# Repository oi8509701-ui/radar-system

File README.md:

X-Band T/R Module (10 GHz) with Fractal Antenna

High-performance single-channel Transmit/Receive (T/R) module for X-band phased array systems (~10–10.5 GHz), featuring integrated beamforming and a compact fractal antenna.
---------------------------------

---------------------------------

High-performance single-channel Transmit/Receive (T/R) module for X-band phased array systems (~10–10.5 GHz), featuring integrated beamforming and a compact fractal antenna.

⸻
 
 Overview

This project implements a single RF front-end module (tile) designed for scalable phased array systems.

Key features:

	•	X-band operation (~10–10.5 GHz)
	•	Integrated PA + LNA + T/R switch (QPM1002)
	•	Beamforming support (phase + amplitude control)
	•	Compact fractal antenna (14×14 mm)
	•	Designed for array scaling (e.g., 256+ elements)
	•	Optimized for automated routing (Freerouting)

⸻
 
 Architecture

RF IN → Phase Shifter → Attenuator → TXIN → [QPM1002] → ANT → Antenna
                                            ▲
RF OUT ← Phase Shifter ← Attenuator ← RXOUT ┘

QPM1002 Internal Structure:

	•	TX path: PA (~35 dBm pulsed)
	•	RX path: LNA (~2.2 dB NF, ~25 dB gain)
	•	Internal T/R switch
	•	Built-in power detector (VDET)

⸻
 
 Power Architecture

Rail	Voltage	Purpose
TX_VD	+25V	Power Amplifier
RX_VD	+10V	LNA
VDD_LOGIC	+5V	Digital logic
VDD_IO	+3.3V	Control interface
VG	-2.5V	GaN gate bias

Converters:

	•	LM5156 (SEPIC) → 25V
	•	LM5017 → 10V / 5V
	•	Charge pump → -2.5V

⸻

RF Components

Component	Function	Notes

QPM1002	T/R front-end	Core RF IC
TGP2109	Phase shifter (6-bit)	8–12 GHz
PE43705	Attenuator (6-bit)	0.5–12 GHz

⸻

 PCB
 
	•	Substrate: Rogers 4350B
	•	Stackup: 4 layers (RF + GND + PWR + CTRL)
	•	Controlled impedance (50 Ω)
	•	Dense via stitching for RF grounding
	•	Optimized for high-frequency layout

⸻

 Thermal Design

Per module dissipation:

Block	Power
PA	~8 W
DC-DC	~5.5 W
Beamforming	~1.3 W
Other	~1 W

Total: ~16 W per module

For 256 modules:

	•	Total ≈ 4 kW
	•	Requires liquid cooling

⸻
 
 Control Interface
 
	•	SPI (phase + attenuation control)
	•	GPIO (TX/RX switching)
	•	I²C (temperature sensors)

Logic:

	•	SN74HC595 (shift register)
	•	SN74LVTH573 (latch)

⸻
 
 Monitoring
 
	•	4× TMP117 temperature sensors:
	•	RF front-end
	•	Power stage
	•	Beamforming chain
	•	PCB ambient

⸻
 
 Power Sequencing

Power-Up:

	1.	Apply VG (-2.5V)
	2.	Disable TX/RX
	3.	Enable RX_VD (10V)
	4.	Enable TX_VD (25V)
	5.	Enable TX/RX

Power-Down:

	1.	Disable TX/RX
	2.	Disable TX_VD
	3.	Disable RX

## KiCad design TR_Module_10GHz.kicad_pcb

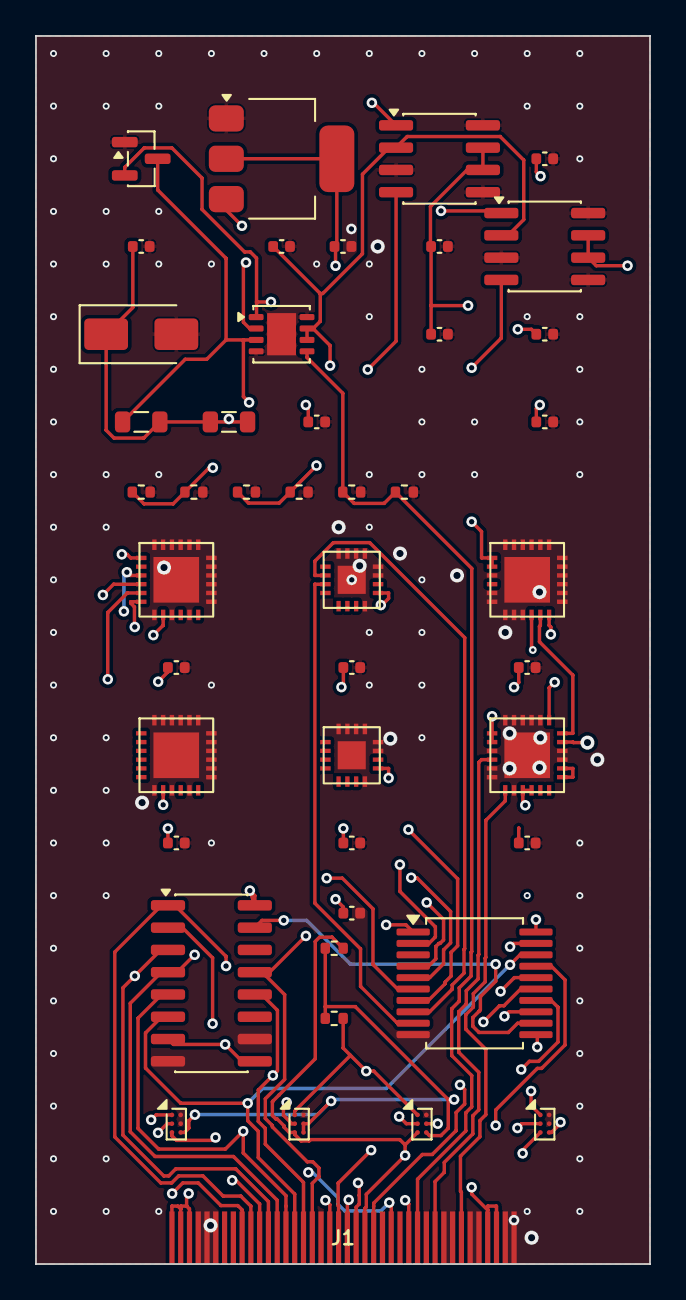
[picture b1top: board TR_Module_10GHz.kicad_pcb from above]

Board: 4 copper layers, 35.0 x 70.0 mm, 45 parts (0 on the bottom side), 39 nets.

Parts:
C10, C11, C12, C13, C14, C15, C16, C17, C18, C19, C20, C21, C22, C23, C24, C25: 100nF; C_0402_1005Metric
D1: TVS; D_SMA
J1: Card Edge 40-pin
L1: EMI; L_0805_2012Metric
L2: 22uH; L_0805_2012Metric
Q1: MOSFET; SOT-23
R1: FB10V_h; R_0402_1005Metric
R2: FB10V_l; R_0402_1005Metric
R3: FB5V_h; R_0402_1005Metric
R4: FB5V_l; R_0402_1005Metric
R5: FBSEP_h; R_0402_1005Metric
R6: FBSEP_l; R_0402_1005Metric
R7: SDA_PU; R_0402_1005Metric
R8: SCL_PU; R_0402_1005Metric
U1: LM5156 SEPIC; VSON-8-1EP_3x3mm_P0.65mm_EP1.65x2.4mm
U2: LM5017 10V; SOIC-8_3.9x4.9mm_P1.27mm
U3: LM5017 5V; SOIC-8_3.9x4.9mm_P1.27mm
U4: ACT43750; QFN-24_4x4mm_P0.5mm
U5: LDO 3.3V; SOT-223-3_TabPin2
U6: QPM1002; QFN-24_4x4mm_P0.5mm
U7: TGP2109 TX; QFN-24_4x4mm_P0.5mm
U8: TGP2109 RX; QFN-24_4x4mm_P0.5mm
U9: QPC0045 TX; QFN-16_3x3mm_P0.5mm
U10: QPC0045 RX; QFN-16_3x3mm_P0.5mm
U11: SN74HC595; SOIC-16_3.9x9.9mm_P1.27mm
U12: SN74LVTH573; SSOP-20_5.3x7.2mm_P0.65mm
U13: TMP117 QPM1002; Texas_DSBGA-6_0.9x1.4mm_Layout2x3_P0.5mm
U14: TMP117 SEPIC; Texas_DSBGA-6_0.9x1.4mm_Layout2x3_P0.5mm
U15: TMP117 PS; Texas_DSBGA-6_0.9x1.4mm_Layout2x3_P0.5mm
U16: TMP117 PCB; Texas_DSBGA-6_0.9x1.4mm_Layout2x3_P0.5mm

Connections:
+3V3: C24.1, C25.1, R7.1, R8.1, U5.2, U13.C2, U14.B2, U14.C2, U15.C2, U16.C2
+5V: C10.1, C13.1, C14.1, C15.1, C16.1, C17.1, C18.1, C19.1, C20.1, C23.1, U3.6, U3.7, U4.1, U4.2, U5.3, U6.1, U6.2, U7.8, U8.8, U9.9, U10.9, U11.16, U12.20, U15.B2
+10V: C12.1, C22.1, U2.6, U2.7, U6.9, U6.10
+25V: U6.13, U6.14
+VIN: C11.1, C21.1, D1.1, J1.1, J1.2, J1.3, J1.37, J1.38, L1.1, L1.2, L2.2, U1.6, U1.7, U2.2, U3.2
BOOT_5V: J1.20, U3.1
BOOT_10V: J1.19, U1.2, U2.1
CTRL_TX_ATT0: U9.2, U12.8
CTRL_TX_ATT1: U9.3, U12.9
CTRL_TX_PS0: U7.1, U12.2
CTRL_TX_PS1: U7.2, U12.3
CTRL_TX_PS2: U7.3, U12.4
CTRL_TX_PS3: U7.4, U12.5
CTRL_TX_PS4: U7.5, U12.6
CTRL_TX_PS5: U7.6, U12.7
EN_BOOST: J1.22, Q1.2, U1.1
FB_5V: J1.28, R3.1, R4.1, U3.4
FB_10V: J1.27, R1.1, R2.1, U2.4
FB_SEPIC: J1.29, R5.1, R6.1, U1.5
GND: C10.2, C11.2, C12.2, C13.2, C14.2, C15.2, C16.2, C17.2, C18.2, C19.2, C20.2, C21.2, C22.2, C23.2, C24.2, C25.2, D1.2, J1.4, J1.5, J1.6, J1.18, J1.30, J1.32, J1.33, J1.35, J1.36, J1.39, J1.40, Q1.1, R1.2, R2.2, R3.2, R4.2, R5.2, R6.2, U1.4, U1.8, U1.9, U2.3, U2.5, U2.8, U3.3, U3.5, U3.8, U4.3, U4.5, U4.6, U4.7, U4.8, U4.9, U4.13, U4.14, U4.15, U4.16, U4.17, U4.18, U4.19, U4.20, U4.21, U4.22, U4.23, U4.24, U4.25, U5.1, U6.3, U6.5, U6.6, U6.8, U6.15, U6.16, U6.20, U6.21, U6.22, U6.23, U6.24, U6.25, U7.7, U7.9, U7.11, U7.13, U7.14, U7.15, U7.16, U7.17, U7.18, U7.19, U7.20, U7.21, U7.22, U7.23, U7.24, U7.25, U8.7, U8.9, U8.11, U8.13, U8.14, U8.15, U8.16, U8.17, U8.18, U8.19, U8.20, U8.21, U8.22, U8.23, U8.24, U8.25, U9.8, U9.11, U9.12, U9.13, U9.14, U9.15, U9.16, U9.17, U10.8, U10.11, U10.12, U10.13, U10.14, U10.15, U10.16, U10.17, U11.8, U11.10, U12.10, U13.A2, U13.B2, U14.A2, U15.A2, U16.A2, U16.B2
I2C_SCL: J1.24, R8.2, U13.A1, U14.A1, U15.A1, U16.A1
I2C_SDA: J1.23, R7.2, U13.C1, U14.C1, U15.C1, U16.C1
RXSW: U4.11, U6.18
RX_RF_OUT: J1.34, U6.7
SR_OE_N: J1.17, U11.13, U12.1
SR_QA: J1.9, U11.15, U12.12
SR_QB: J1.10, U11.1, U12.13
SR_QC: J1.11, U11.2, U12.14
SR_QD: J1.12, U11.3, U12.15
SR_QE: J1.13, U11.4, U12.16
SR_QF: J1.14, U11.5, U12.17
SR_QG: J1.15, U11.6, U12.18
SR_QH: U11.7, U11.9, U12.19
SR_RCLK: J1.16, U11.12, U12.11
SW_SEPIC: J1.26, L2.1, Q1.3, U1.3
TMP_ALERT: J1.25, U13.B1, U14.B1, U15.B1, U16.B1
TXSW: U4.10, U6.17
TX_RF_IN: J1.31, U6.4
VG: J1.21, U4.12, U6.19

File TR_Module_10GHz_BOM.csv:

value,footprint,quantity,references
100nF,Capacitor_SMD:C_0402_1005Metric,11,"['C20', 'C19', 'C18', 'C17', 'C16', 'C15', 'C14', 'C13', 'C12', 'C11', 'C10']"
SN74LVTH573,Package_SO:SSOP-20_5.3x7.2mm_P0.65mm,1,['U12']
SN74HC595,Package_SO:SOIC-16_3.9x9.9mm_P1.27mm,1,['U11']
MountingHole_2.7mm,,4,"['MH2', 'MH3', 'MH1', 'MH4']"
TMP117 SEPIC,Package_BGA:Texas_DSBGA-6_0.9x1.4mm_Layout2x3_P0.5mm,1,['U14']
TMP117 PS,Package_BGA:Texas_DSBGA-6_0.9x1.4mm_Layout2x3_P0.5mm,1,['U15']
QPC0045 TX,TR_Module_Lib:QFN-16_3x3mm_P0.5mm,1,['U9']
LM5017 10V,Package_SO:SOIC-8_3.9x4.9mm_P1.27mm,1,['U2']
LM5156 SEPIC,Package_SON:VSON-8-1EP_3x3mm_P0.65mm_EP1.65x2.4mm,1,['U1']
QPM1002,TR_Module_Lib:QFN-24_4x4mm_P0.5mm,1,['U6']
LM5017 5V,Package_SO:SOIC-8_3.9x4.9mm_P1.27mm,1,['U3']
TGP2109 TX,TR_Module_Lib:QFN-24_4x4mm_P0.5mm,1,['U7']
TGP2109 RX,TR_Module_Lib:QFN-24_4x4mm_P0.5mm,1,['U8']
ACT43750,TR_Module_Lib:QFN-24_4x4mm_P0.5mm,1,['U4']
TMP117 QPM1002,Package_BGA:Texas_DSBGA-6_0.9x1.4mm_Layout2x3_P0.5mm,1,['U13']
QPC0045 RX,TR_Module_Lib:QFN-16_3x3mm_P0.5mm,1,['U10']
TMP117 PCB,Package_BGA:Texas_DSBGA-6_0.9x1.4mm_Layout2x3_P0.5mm,1,['U16']

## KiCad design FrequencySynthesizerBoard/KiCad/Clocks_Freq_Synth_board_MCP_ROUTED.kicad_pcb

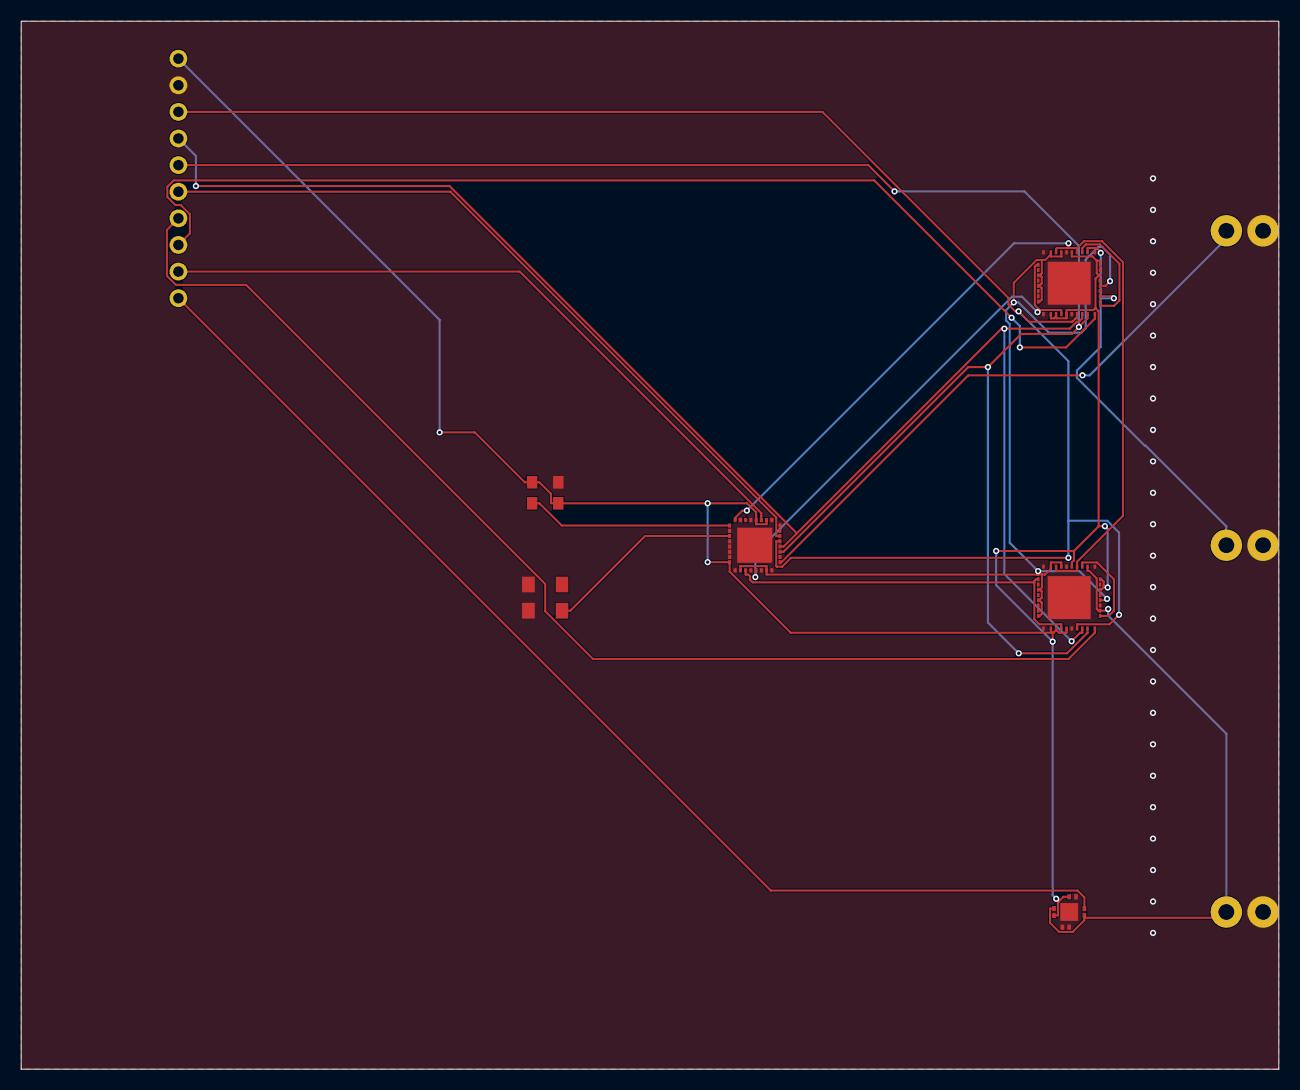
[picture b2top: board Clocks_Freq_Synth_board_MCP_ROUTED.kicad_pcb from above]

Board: 2 copper layers, 120.0 x 100.0 mm, 10 parts (0 on the bottom side), 21 nets.

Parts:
J1: SMA_TX_LO; SMA_Amphenol_132133-01-2X_Horizontal
J2: SMA_RX_LO; SMA_Amphenol_132133-01-2X_Horizontal
J3: SMA_REF_OUT; SMA_Amphenol_132133-01-2X_Horizontal
J4: CTRL_INTERFACE; PinSocket_1x10_P1.27mm_Vertical
U1: AD9523-1; LFCS-32-1EP_5x5mm_P0.5mm_EP3.35x3.35mm
U2, U3: ADF4382ABCCZ; LFCC-40-1EP_6x6mm_P0.5mm_EP4.1x4.1mm
U4: HMC1118; LFCS-8-1EP_3x3mm_P0.65mm_EP1.7x1.7mm
Y1: 100MHz OCXO; Oscillator_SMD_EuropeanQuartz_3225-4Pin
Y2: 25MHz TCXO; Oscillator_SMD_EuropeanQuartz_2520-4Pin

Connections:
CLK_25M: U1.1, Y2.4
CLK_100M: U1.3, Y1.3
CLK_DIST_RX: U1.13, U3.1, U3.12
CLK_DIST_TX: U1.11, U2.1, U2.12
CS_U1: J4.6, U1.22
CS_U2: J4.7, U2.18
CS_U3: J4.8, U3.18
GND: J1.2, J2.2, J3.2, J4.2, U1.2, U1.4, U1.5, U1.6, U1.7, U1.9, U1.12, U1.14, U1.16, U1.18, U1.24, U1.25, U1.29, U1.31, U1.EP, U2.2, U2.4, U2.6, U2.7, U2.9, U2.14, U2.21, U2.23, U2.25, U2.27, U2.32, U2.36, U2.EP, U3.2, U3.4, U3.6, U3.7, U3.9, U3.14, U3.21, U3.23, U3.25, U3.27, U3.32, U3.36, U3.EP, U4.3, U4.4, U4.7, U4.EP, Y1.1, Y1.4, Y2.2
RF_REF: J3.1, U1.17
RF_RX_N: U3.19, U3.29
RF_RX_P: J2.1, U3.20, U3.28
RF_SW_CTRL: J4.10, U4.6
RF_TX_N: U2.19, U2.29
RF_TX_P: J1.1, U2.20, U2.28, U4.1, U4.5
SPI_CLK: J4.3, U1.21, U2.15, U3.15
SPI_MISO: J4.5, U1.19, U2.17, U3.17
SPI_MOSI: J4.4, U1.20, U2.16, U3.16
U1_SYNC: J4.9, U1.27
VCP: U1.32, U2.30, U2.34, U3.30, U3.34
VDD_1V8: U1.10, U1.15, U1.30, U2.3, U2.5, U2.8, U2.22, U2.33, U2.35, U3.3, U3.5, U3.8, U3.22, U3.33, U3.35
VDD_3V3: J4.1, U1.8, U1.26, U1.28, U2.10, U2.11, U2.13, U2.24, U2.26, U2.31, U3.10, U3.11, U3.13, U3.24, U3.26, U3.31, U4.2, U4.8, Y2.1, Y2.3

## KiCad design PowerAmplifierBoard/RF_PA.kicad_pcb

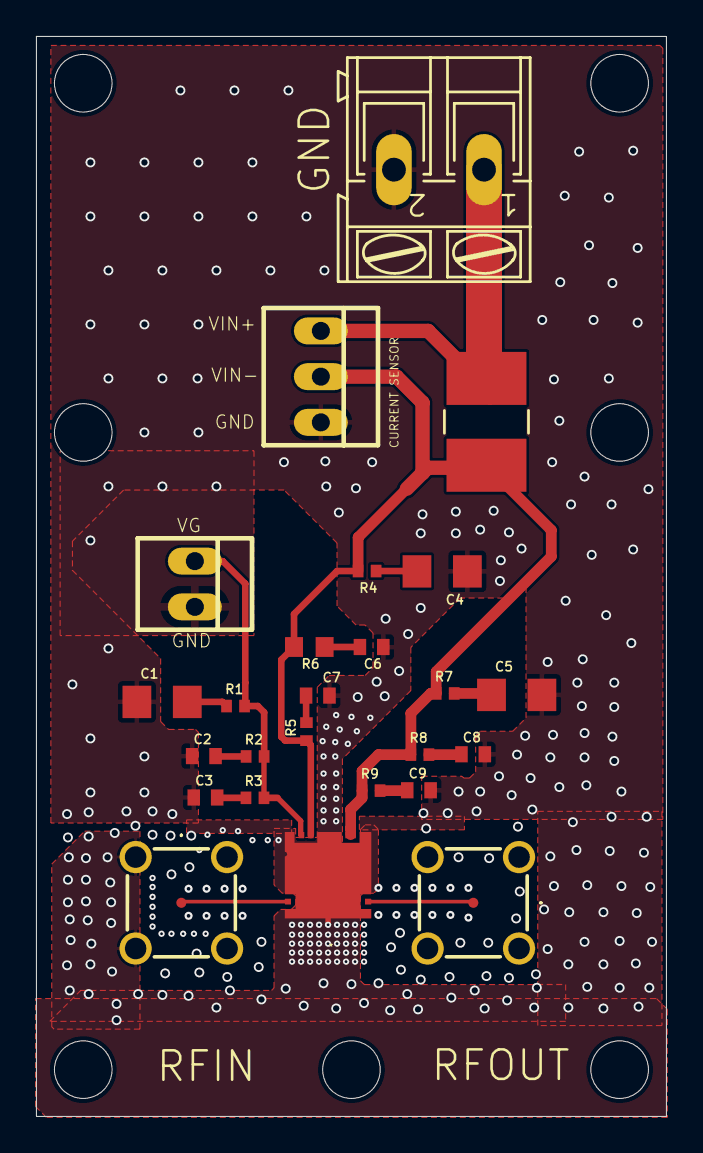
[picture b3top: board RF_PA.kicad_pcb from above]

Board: 4 copper layers, 35.0 x 60.0 mm, 32 parts (0 on the bottom side), 15 nets.

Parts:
C1, C4, C5: 10µF; C1206_334
C2, C3, C6, C7, C8, C9: 0.1µF; C0402_334
J1, J2: 142-0731-211; 1420731211
R1, R4: 10R; R0402_334
R2, R3, R5, R7, R8, R9: 0R; R0402_334
R6: 0R; R0603_334
R10: 5mR; WSL2816_VIS
U$1: QPA2962_B
UNK22V0: AK300_2_181
UNK_HOLE_0: dummyfp0
UNK_HOLE_1: dummyfp1
UNK_HOLE_2: dummyfp2
UNK_HOLE_3: dummyfp3
UNK_HOLE_4: dummyfp4
UNK_HOLE_5: dummyfp5
UNK_HOLE_6: dummyfp6
X2: 22-23-2021; 22-23-2021_165
X3: 22-23-2031; 22-23-2031_165

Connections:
GND: C1.1, C2.1, C3.1, C4.1, C5.2, C6.1, C7.1, C8.2, C9.2, J1.2, J1.3, J1.4, J1.5, J2.2, J2.3, J2.4, J2.5, U$1.GND, UNK22V0.2, X2.2, X3.3
unnamed: C3.2, R3.1
unnamed: J1.1, U$1.RFIN
unnamed: C1.2, R1.1
unnamed: C2.2, R2.1
unnamed: C4.2, R4.1
unnamed: C6.2, R6.1
unnamed: C7.2, R5.1
unnamed: J2.1, U$1.RFOUT
unnamed: C5.1, R7.2
unnamed: C8.1, R8.2
unnamed: C9.1, R9.2
VD: R10.2, UNK22V0.1, X3.1
VG: R1.2, R2.2, R3.2, U$1.VG, X2.1
VIN_M: R4.2, R5.2, R6.2, R7.1, R8.1, R9.1, R10.1, U$1.VD1, U$1.VD2, X3.2

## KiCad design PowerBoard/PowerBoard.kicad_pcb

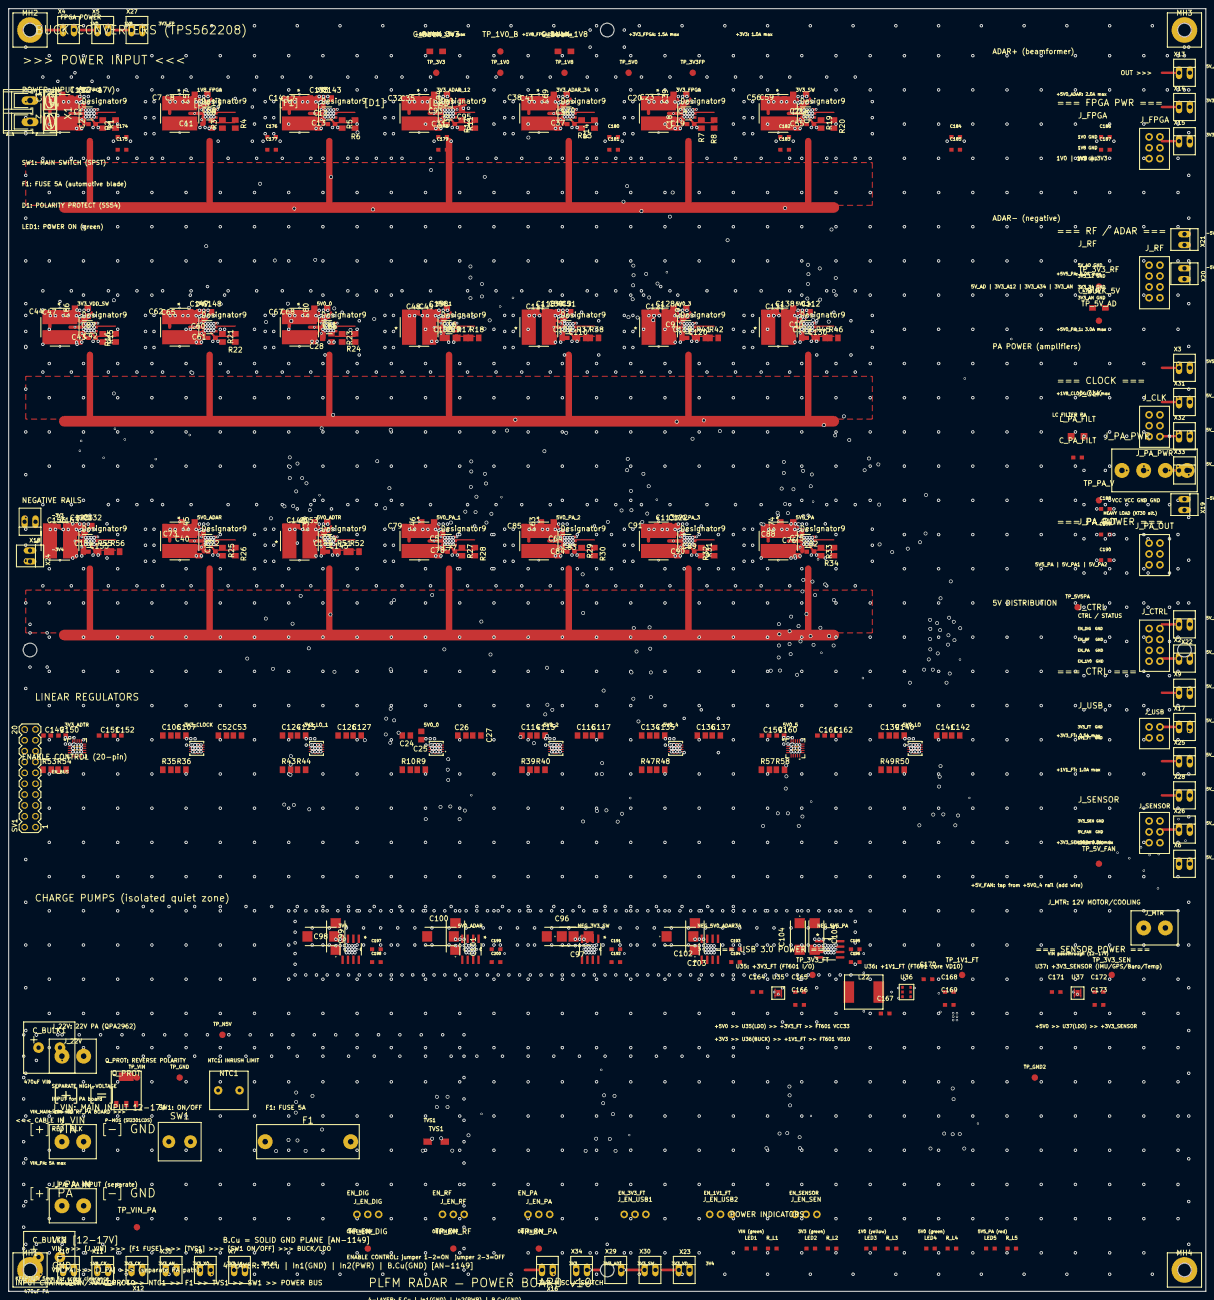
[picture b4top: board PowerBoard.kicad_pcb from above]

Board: 2 copper layers, 280.0 x 300.0 mm, 427 parts (0 on the bottom side), 163 nets.

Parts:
C1, C6, C12, C18, C29, C30, C36, C42, C54, C60, C66, C71, C76, C77, C83, C89, C109, C119, C129, C144, C154: 0.1µF; C0805
C2, C3, C7, C8, C11, C13, C14, C17, C19, C20, C23, C31, C32, C35, C37, C38, C41, C43, C44, C47, C48, C49, C55, C56, C59, C61, C62, C65, C67, C68, C72, C73, C78, C79, C82, C84, C85, C88, C90, C91, C110, C111, C120, C121, C130, C131, C145, C146, C149, C155, C156, C159: 22µF; C0603
C4, C5, C9, C10, C15, C16, C21, C22, C24, C25, C28, C33, C34, C39, C40, C45, C46, C50, C51, C52, C53, C57, C58, C63, C64, C69, C70, C74, C75, C80, C81, C86, C87, C92, C93, C94, C95, C108, C112, C113, C114, C115, C118, C122, C123, C124, C125, C128, C132, C133, C134, C135, C138, C139, C140, C143, C147, C148, C157, C158: 10µF; C0805
C26, C27, C106, C107, C116, C117, C126, C127, C136, C137, C141, C142: 1µF; C0805
C96, C97, C98, C99, C100, C101, C102, C103, C104, C105: T521W476M020ATE045; T521W
C150, C152, C160, C162: 10nF; C0603
C151, C153, C161, C163: 10µF; C0603
C164, C165, C167, C171, C172: 10uF; C0805
C166, C173: 1uF; C0805
C168, C169: 22uF; C0805
C170: 100nF; C0805
C174, C176, C178, C180, C182, C184, C186: 10uF VIN; C0805_BUS
C175, C177, C179, C181, C183, C185, C187: 100nF VIN; C0805_BUS
C188: 47uF PA; C0805_BUS
C189: 10uF PA; C0805_BUS
C190: 100nF PA; C0805_BUS
C191: 10uF -3V3_SW; C0805_FILT
C192: 100nF -3V3_SW; C0805_FILT
C193: 10uF -5V0_ADAR34; C0805_FILT
C194: 100nF -5V0_ADAR34; C0805_FILT
C195: 10uF -5V5_PA; C0805_FILT
C196: 100nF -5V5_PA; C0805_FILT
C197: 10uF -3V4; C0805_FILT
C198: 100nF -3V4; C0805_FILT
C199: 10uF -5V0_ADAR12; C0805_FILT
C200: 100nF -5V0_ADAR12; C0805_FILT
C_BULK1, C_BULK2: 470uF/25V; Capacitor_THT_D10_P5mm
C_BULK_1V8: 22uF/6.3V; Cap_1210_22uF
C_BULK_3V3: 47uF/6.3V; Cap_1210_47uF
C_BULK_5V: 47uF/10V; Cap_1210_47uF
C_PA_FILT: 10uF/10V; Cap_0805_PA
F1: FUSE 5A; Fuse_Holder_5x20
J_22V: 22V PA INPUT; AK300_2_NEW
J_CLK: CLOCK_PWR; PinHeader_2xN_P2.54mm
J_CTRL: CTRL/STATUS; PinHeader_2x4_P2.54mm
J_EN_DIG: EN_DIGITAL; Jumper_1x03_P2.54mm
J_EN_PA: EN_PA; Jumper_1x03_P2.54mm
J_EN_RF: EN_RF; Jumper_1x03_P2.54mm
J_EN_SEN: EN_SENSOR; Jumper_1x03_P2.54mm
J_EN_USB1: EN_3V3_FT; Jumper_1x03_P2.54mm
J_EN_USB2: EN_1V1_FT; Jumper_1x03_P2.54mm
J_FPGA: FPGA_PWR; PinHeader_2xN_P2.54mm
J_MTR: MOTOR/FAN 12V; AK300_2_NEW
J_PA_IN: VIN_PA; AK300_2_NEW
J_PA_OUT: PA_PWR; PinHeader_2xN_P2.54mm
J_PA_PWR: PA_POWER_OUT; ScrewTerminal_4pin_5.08mm
J_RF: RF_ADAR_PWR; PinHeader_2xN_P2.54mm
J_SENSOR: SENSOR_PWR; PinHeader_2xN_P2.54mm
J_USB: USB_PWR; PinHeader_2xN_P2.54mm
J_VIN: VIN_MAIN 12-17V; AK300_2_NEW
L1, L9: 2.2µH; IND_VLP8040T-1R0N_TDK
L2, L3, L4, L5, L6, L7, L8, L10, L11, L12, L13, L14, L15, L16, L17, L18, L19, L20, L21: 3.3µH; IND_VLP8040T-1R0N_TDK
L22: 1uH; IND_VLP8040T
LED1, LED2, LED3, LED4, LED5: LED; LED_0805
L_PA_FILT: 4.7uH/3A; Inductor_1210
MH1, MH2, MH3, MH4: M3; MountingHole_M3
NTC1: 5D-9 NTC; NTC_Radial_5mm
Q_PROT: Si2301CDS; SOT-223_P-MOS
R1: 3.09k; M0805
R2, R4, R6, R8, R10, R12, R14, R16, R18, R20, R22, R24, R26, R28, R30, R32, R34, R36, R38, R40, R42, R44, R46, R48, R50, R52, R56: 10k; M0805
R3: 13.7k; M0805
R5, R7, R11, R13, R15, R19: 32.2k; M0805
R9, R35, R43, R47: 12k; M0805
R17, R23, R25, R27, R29, R31, R37, R41, R45, R51, R55: 56.2k; M0805
R21: 34.8k; M0805
R33: 61.9k; M0805
R39: 2k; M0805
R49: 23.4k; M0805
R53, R57: 35.7k; M0805
R54, R58: 11.5k; M0805
R_L1, R_L2, R_L3, R_L4, R_L5: 1k; R_0805_LED
SV1: MA10-2
SW1: MAIN POWER; SW_SPST_Toggle
TP_1V0, TP_1V0_B: +1V0_FPGA; TestPoint_1.5mm
TP_1V1_FT: +1V1_FT; TestPoint_1.5mm
TP_1V8: +1V8_FPGA; TestPoint_1.5mm
TP_3V3: +3V3; TestPoint_1.5mm
TP_3V3FP: +3V3_FPGA; TestPoint_1.5mm
TP_3V3_FT: +3V3_FT; TestPoint_1.5mm
TP_3V3_RF: +3V3_ADAR_12; TestPoint_1.5mm
TP_3V3_SEN: +3V3_SENSOR; TestPoint_1.5mm
TP_5V0: +5V0_4; TestPoint_1.5mm
TP_5V5PA: +5V5_PA; TestPoint_1.5mm
TP_5V_AD: +5V0_ADAR; TestPoint_1.5mm
TP_5V_FAN: +5V_FAN; TestPoint_1.5mm
TP_EN_DIG: EN_+3V3_FPGA; TestPoint_1.5mm
TP_EN_PA: EN_+5V5_PA; TestPoint_1.5mm
TP_EN_RF: EN_+5V0_ADAR; TestPoint_1.5mm
TP_GND, TP_GND2: GND; TestPoint_1.5mm
TP_N5V: -5V0_ADAR12; TestPoint_1.5mm
TP_PA_V: +5V5_PA; TestPoint_1.5mm
TP_VIN: VIN; TestPoint_1.5mm
TP_VIN_PA: VIN; TestPoint_1.5mm
TVS1: SMAJ18A; TVS_SMA
U1, U2, U3, U4, U6, U7, U8, U9, U10, U11, U12, U13, U14, U15, U16, U17, U24, U26, U28, U31, U33: TPS562208DDCT; DDC0006A_N
U5, U23, U25, U27, U29, U30: ADM7151ACPZ-04-R7; CP_8_11_ADI
U18, U19, U20, U21, U22: LM2662MX/NOPB; M08A
U32, U34: TPS7A8300RGRR; RGR20_2P05X2P05_TEX
U35: ADM7151 3V3_FT; CP_8_11_ADI
U36: TPS562208 1V1_FT; DDC0006A_N
U37: ADM7151 3V3_SEN; CP_8_11_ADI
UNK_HOLE_0: dummyfp0
UNK_HOLE_1: dummyfp1
UNK_HOLE_2: dummyfp2
UNK_HOLE_3: dummyfp3
UNK_HOLE_4: dummyfp4
UNK_HOLE_5: dummyfp5
UNK_HOLE_6: dummyfp6
UNK_HOLE_7: dummyfp7
X1: AK300_2
X2, X3, X4, X5, X6, X7, X8, X9, X10, X11, X12, X13, X14, X15, X16, X17, X18, X19, X20, X21, X22, X23, X24, X25, X26, X27, X28, X29, X30, X31, X32, X33, X34, X35: 22-23-2021

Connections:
+1V0_FPGA: C2.1, C3.1, J_FPGA.1, L1.1, LED3.1, R1.2, R_L3.1, R_L3.2, TP_1V0.1, TP_1V0_B.1, X4.1
+1V1_FT: C168.1, C169.1, C170.1, J_USB.3, L22.1, L22.2, TP_1V1_FT.1, U36.2, U36.5, U36.6
+1V8_CLOCK: C115.2, J_CLK.1, U25.2, X10.1
+1V8_FPGA: C7.1, C8.1, C11.1, C_BULK_1V8.1, J_FPGA.3, L9.1, R3.2, TP_1V8.1, X5.1
+3V3: C13.1, C14.1, C17.1, C167.1, L11.1, LED2.1, R5.2, R_L2.1, R_L2.2, TP_3V3.1, U36.3, X16.1
+3V3_ADAR_12: C31.1, C32.1, C35.1, J_RF.3, L14.1, R11.2, TP_3V3_RF.1, X14.1
+3V3_ADAR_34: C37.1, C38.1, C41.1, J_RF.5, L15.1, R13.2, X15.1
+3V3_ADTR: C149.1, R53.2, U32.1, U32.19, U32.20, X34.1
+3V3_AN: C25.2, J_RF.7, U5.2, X12.1
+3V3_CLOCK: C53.2, J_CLK.3, U23.2, X11.1
+3V3_FPGA: C19.1, C20.1, C23.1, C_BULK_3V3.1, J_FPGA.5, L7.1, R7.2, TP_3V3FP.1, X27.1
+3V3_FT: C165.1, C166.1, J_USB.1, TP_3V3_FT.1, U35.3, U35.4, U35.5
+3V3_LO_1: C125.2, U27.2, X8.1
+3V3_LO_2: C135.2, U29.2, X7.1
+3V3_SENSOR: C172.1, C173.1, J_SENSOR.1, TP_3V3_SEN.1, U37.3, U37.4, U37.5
+3V3_SW: C55.1, C56.1, C59.1, L3.1, R19.2, U18.8, X29.1
+3V3_VDD_SW: C43.1, C44.1, C47.1, L16.1, R15.2, X30.1
+3V3_XO: C159.1, J_CLK.5, R57.2, U34.1, U34.19, U34.20, X35.1
+3V4: C61.1, C62.1, C65.1, L10.1, R21.2, U19.8, X23.1
+5V0_0: C28.2, C67.1, C68.1, L20.1, R23.2, U5.7, U5.8, X22.1
+5V0_1: C48.1, C49.1, C108.2, L4.1, R17.2, U23.8, X2.1
+5V0_2: C110.1, C111.1, C118.2, L5.1, R37.2, U25.8, X9.1
+5V0_3: C120.1, C121.1, C128.2, L2.1, R41.2, U27.7, U27.8, X17.1
+5V0_4: C130.1, C131.1, C138.2, C164.1, C171.1, L12.1, LED4.1, R45.2, R_L4.1, R_L4.2, TP_5V0.1, U29.7, U29.8, U35.7, U35.8, U37.7, U37.8, X25.1
+5V0_5: C155.1, C156.1, C163.1, L21.1, R55.2, U34.14, U34.15, U34.16, U34.17, X28.1
+5V0_ADAR: C72.1, C73.1, C_BULK_5V.1, J_RF.1, L8.1, R25.2, TP_5V_AD.1, U20.8, U21.8, X13.1
+5V0_ADTR: C145.1, C146.1, C153.1, L6.1, R51.2, U32.15, U32.16, U32.17, X26.1
+5V0_LO: C140.2, U30.2, X6.1
+5V0_PA_1: C78.1, C79.1, J_PA_OUT.3, L18.1, R27.2, X31.1
+5V0_PA_2: C84.1, C85.1, J_PA_OUT.5, L17.1, R29.2, X32.1
+5V0_PA_3: C90.1, C91.1, L13.1, R31.2, X33.1
+5V5_PA: C82.1, C88.1, C188.1, C189.1, C190.1, C_PA_FILT.1, J_PA_OUT.1, J_PA_PWR.1, J_PA_PWR.2, L19.1, LED5.1, L_PA_FILT.1, L_PA_FILT.2, R33.2, R_L5.1, R_L5.2, TP_5V5PA.1, TP_PA_V.1, U22.8, X3.1
+5V_FAN: J_SENSOR.3, TP_5V_FAN.1
-3V3_SW: C97.2, C191.1, C192.1, U18.5, X18.1
-3V4: C99.2, C197.1, C198.1, U19.5, X24.1
-5V0_ADAR12: C101.2, C199.1, C200.1, TP_N5V.1, U20.5, X21.1
-5V0_ADAR34: C103.2, C193.1, C194.1, U21.5, X20.1
-5V5_PA: C105.2, C195.1, C196.1, U22.5, X19.1
EN_+1V0_FPGA: J_CTRL.7, SV1.1, U1.5
EN_+1V1_FT: J_EN_USB2.1, U36.4
EN_+1V8_CLOCK: SV1.8, U25.7
EN_+1V8_FPGA: SV1.3, U2.5
EN_+3V3_ADAR12: SV1.9, U6.5
EN_+3V3_ADAR34: SV1.11, U7.5
EN_+3V3_ADTR: SV1.13, U32.14
EN_+3V3_CLOCK: SV1.10, U23.7
EN_+3V3_FPGA: J_CTRL.1, J_EN_DIG.1, SV1.5, TP_EN_DIG.1, U4.5
EN_+3V3_FT: J_EN_USB1.1, U35.1
EN_+3V3_SENSOR: J_EN_SEN.1, U37.1
EN_+3V3_SW: SV1.15, U10.5
EN_+3V3_VDD_SW: SV1.17, U8.5
EN_+5V0_ADAR: J_CTRL.3, J_EN_RF.1, SV1.7, TP_EN_RF.1, U13.5
EN_+5V0_PA1: SV1.19, U14.5
EN_+5V0_PA2: SV1.2, U15.5
EN_+5V0_PA3: SV1.4, U16.5
EN_+5V5_PA: J_CTRL.5, J_EN_PA.1, SV1.6, TP_EN_PA.1, U17.5
GND: C2.2, C3.2, C4.2, C5.2, C7.2, C8.2, C9.2, C10.2, C11.2, C13.2, C14.2, C15.2, C16.2, C17.2, C19.2, C20.2, C21.2, C22.2, C23.2, C24.1, C25.1, C26.1, C27.1, C28.1, C31.2, C32.2, C33.2, C34.2, C35.2, C37.2, C38.2, C39.2, C40.2, C41.2, C43.2, C44.2, C45.2, C46.2, C47.2, C48.2, C49.2, C50.2, C51.2, C52.1, C53.1, C55.2, C56.2, C57.2, C58.2, C59.2, C61.2, C62.2, C63.2, C64.2, C65.2, C67.2, C68.2, C69.2, C70.2, C72.2, C73.2, C74.2, C75.2, C78.2, C79.2, C80.2, C81.2, C82.2, C84.2, C85.2, C86.2, C87.2, C88.2, C90.2, C91.2, C92.2, C93.2, C94.2, C95.2, C97.1, C99.1, C101.1, C103.1, C105.1, C106.1, C107.1, C108.1, C110.2, C111.2, C112.2, C113.2, C114.1, C115.1, C116.1, C117.1, C118.1, C120.2, C121.2, C122.2, C123.2, C124.1, C125.1, C126.1, C127.1, C128.1, C130.2, C131.2, C132.2, C133.2, C134.1, C135.1, C136.1, C137.1, C138.1, C139.1, C140.1, C141.1, C142.1, C143.1, C145.2, C146.2, C147.2, C148.2, C149.2, C151.2, C152.2, C153.2, C155.2, C156.2, C157.2, C158.2, C159.2, C161.2, C162.2, C163.2, C164.2, C165.2, C166.2, C167.2, C168.2, C169.2, C170.2, C171.2, C172.2, C173.2, C174.2, C175.2, C176.2, C177.2, C178.2, C179.2, C180.2, C181.2, C182.2, C183.2, C184.2, C185.2, C186.2, C187.2, C188.2, C189.2, C190.2, C191.2, C192.2, C193.2, C194.2, C195.2, C196.2, C197.2, C198.2, C199.2, C200.2, C_BULK1.2, C_BULK2.2, C_BULK_1V8.2, C_BULK_3V3.2, C_BULK_5V.2, C_PA_FILT.2, J_22V.2, J_CLK.2, J_CLK.4, J_CLK.6, J_CTRL.2, J_CTRL.4, J_CTRL.6, J_CTRL.8, J_EN_DIG.3, J_EN_PA.3, J_EN_RF.3, J_EN_SEN.3, J_EN_USB1.3, J_EN_USB2.3, J_FPGA.2, J_FPGA.4, J_FPGA.6, J_MTR.2, J_PA_IN.2, J_PA_OUT.2, J_PA_OUT.4, J_PA_OUT.6, J_PA_PWR.3, J_PA_PWR.4, J_RF.2, J_RF.4, J_RF.6, J_RF.8, J_SENSOR.2, J_SENSOR.4, J_SENSOR.6, J_USB.2, J_USB.4, J_VIN.2, LED1.2, LED2.2, LED3.2, LED4.2, LED5.2, MH1.1, MH2.1, MH3.1, MH4.1, Q_PROT.1, R2.1, R4.1, R6.1, R8.1, R10.1, R12.1, R14.1, R16.1, R18.1, R20.1, R22.1, R24.1, R26.1, R28.1, R30.1, R32.1, R34.1, R36.1, R38.1, R40.1, R42.1, R44.1, R46.1, R48.1, R50.1, R52.1, R54.1, R56.1, R58.1, SV1.12, SV1.14, SV1.16, SV1.18, SV1.20, TP_GND.1, TP_GND2.1, TVS1.2, U1.1, U2.1, U3.1, U4.1, U5.4, U5.9, U6.1, U7.1, U8.1, U9.1, U10.1, U11.1, U12.1, U13.1, U14.1, U15.1, U16.1, U17.1, U18.3, U18.6, U19.3, U19.6, U20.3, U20.6, U21.3, U21.6, U22.3, U22.6, U23.4, U23.9, U24.1, U25.4, U25.9, U26.1, U27.4, U27.9, U28.1, U29.4, U29.9, U30.4, U30.9, U31.1, U32.8, U32.18, U32.21, U33.1, U34.8, U34.18, U34.21, U35.2, U35.6, U35.9, U36.1, U37.2, U37.6, U37.9, X1.2, X2.2, X3.2, X4.2, X5.2, X6.2, X7.2, X8.2, X9.2, X10.2, X11.2, X12.2, X13.2, X14.2, X15.2, X16.2, X17.2, X18.2, X19.2, X20.2, X21.2, X22.2, X23.2, X24.2, X25.2, X26.2, X27.2, X28.2, X29.2, X30.2, X31.2, X32.2, X33.2, X34.2, X35.2
unnamed: C1.2, L1.2, U1.2
unnamed: C1.1, U1.6
unnamed: C6.2, L9.2, U2.2
unnamed: R1.1, R2.2, U1.4
unnamed: C6.1, U2.6
unnamed: R3.1, R4.2, U2.4
unnamed: C12.2, L11.2, U3.2
unnamed: C12.1, U3.6
unnamed: R5.1, R6.2, U3.4
unnamed: C18.2, L7.2, U4.2
unnamed: C18.1, U4.6
unnamed: R7.1, R8.2, U4.4
unnamed: C24.2, U5.1
unnamed: C139.2, U30.1
unnamed: C26.2, U5.3
unnamed: C30.2, L14.2, U6.2
unnamed: C30.1, U6.6
unnamed: R11.1, R12.2, U6.4
unnamed: C36.2, L15.2, U7.2
unnamed: C36.1, U7.6
unnamed: R13.1, R14.2, U7.4
unnamed: C42.2, L16.2, U8.2
unnamed: C42.1, U8.6
unnamed: R15.1, R16.2, U8.4
unnamed: R9.1, R10.2, U5.5
unnamed: C29.2, L4.2, U9.2
unnamed: C27.2, R9.2, U5.6
unnamed: C54.2, L3.2, U10.2
unnamed: C54.1, U10.6
unnamed: R19.1, R20.2, U10.4
unnamed: C60.2, L10.2, U11.2
unnamed: C60.1, U11.6
unnamed: R21.1, R22.2, U11.4
unnamed: C66.2, L20.2, U12.2
unnamed: C66.1, U12.6
unnamed: R23.1, R24.2, U12.4
unnamed: C71.2, L8.2, U13.2
unnamed: C71.1, U13.6
unnamed: R25.1, R26.2, U13.4
unnamed: C77.2, L18.2, U14.2
unnamed: C77.1, U14.6
unnamed: R27.1, R28.2, U14.4
unnamed: C83.2, L17.2, U15.2
unnamed: C83.1, U15.6
unnamed: R29.1, R30.2, U15.4
unnamed: C89.2, L13.2, U16.2
unnamed: C89.1, U16.6
unnamed: R31.1, R32.2, U16.4
unnamed: C76.2, L19.2, U17.2
unnamed: C76.1, U17.6
unnamed: R33.1, R34.2, U17.4
unnamed: C98.1, U19.2
unnamed: C98.2, U19.4
unnamed: C96.1, U18.2
unnamed: C96.2, U18.4
unnamed: C100.1, U20.2
unnamed: C100.2, U20.4
unnamed: C102.1, U21.2
unnamed: C102.2, U21.4
unnamed: C104.1, U22.2
unnamed: C104.2, U22.4
unnamed: C141.2, U30.3
unnamed: R49.1, R50.2, U30.5
unnamed: C29.1, U9.6
unnamed: R17.1, R18.2, U9.4
unnamed: C52.2, U23.1
unnamed: C142.2, R49.2, U30.6
unnamed: C106.2, U23.3
unnamed: R35.1, R36.2, U23.5
unnamed: C107.2, R35.2, U23.6
unnamed: C144.2, L6.2, U31.2
unnamed: C144.1, U31.6
unnamed: C109.2, L5.2, U24.2
unnamed: C109.1, U24.6
unnamed: R37.1, R38.2, U24.4
unnamed: C114.2, U25.1
unnamed: R51.1, R52.2, U31.4
unnamed: C116.2, U25.3
unnamed: R39.1, R40.2, U25.5
unnamed: C117.2, R39.2, U25.6
unnamed: C154.2, L21.2, U33.2
unnamed: C150.1, U32.2
unnamed: C119.2, L2.2, U26.2
unnamed: C119.1, U26.6
unnamed: R41.1, R42.2, U26.4
unnamed: C124.2, U27.1
unnamed: C154.1, U33.6
unnamed: C126.2, U27.3
unnamed: R43.1, R44.2, U27.5
unnamed: C127.2, R43.2, U27.6
unnamed: C150.2, R53.1, R54.2, U32.3
unnamed: C151.1, U32.12
unnamed: C129.2, L12.2, U28.2
unnamed: C129.1, U28.6
unnamed: R45.1, R46.2, U28.4
unnamed: C134.2, U29.1
unnamed: R55.1, R56.2, U33.4
unnamed: C136.2, U29.3
unnamed: R47.1, R48.2, U29.5
unnamed: C137.2, R47.2, U29.6
unnamed: C152.1, U32.13
unnamed: C160.1, U34.2
unnamed: C160.2, R57.1, R58.2, U34.3
unnamed: C161.1, U34.12
unnamed: C162.1, U34.13
VIN: C4.1, C5.1, C9.1, C10.1, C15.1, C16.1, C21.1, C22.1, C33.1, C34.1, C39.1, C40.1, C45.1, C46.1, C50.1, C51.1, C57.1, C58.1, C63.1, C64.1, C69.1, C70.1, C74.1, C75.1, C80.1, C81.1, C86.1, C87.1, C92.1, C93.1, C94.1, C95.1, C112.1, C113.1, C122.1, C123.1, C132.1, C133.1, C143.2, C147.1, C148.1, C157.1, C158.1, C174.1, C175.1, C176.1, C177.1, C178.1, C179.1, C180.1, C181.1, C182.1, C183.1, C184.1, C185.1, C186.1, C187.1, C_BULK1.1, C_BULK2.1, F1.1, F1.2, J_22V.1, J_EN_DIG.2, J_EN_PA.2, J_EN_RF.2, J_EN_SEN.2, J_EN_USB1.2, J_EN_USB2.2, J_MTR.1, J_PA_IN.1, J_SENSOR.5, J_VIN.1, LED1.1, NTC1.1, NTC1.2, Q_PROT.2, Q_PROT.3, Q_PROT.4, R_L1.1, R_L1.2, SW1.1, SW1.2, TP_VIN.1, TP_VIN_PA.1, TVS1.1, U1.3, U2.3, U3.3, U3.5, U4.3, U6.3, U7.3, U8.3, U9.3, U9.5, U10.3, U11.3, U11.5, U12.3, U12.5, U13.3, U14.3, U15.3, U16.3, U17.3, U24.3, U24.5, U26.3, U26.5, U28.3, U28.5, U30.7, U30.8, U31.3, U31.5, U33.3, U33.5, X1.1

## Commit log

2026-03-31 Initial commit: Fractal 32x16 antenna array with simulation reports and images
2026-03-31 Add README.md with simulation results and specifications
2026-03-31 Add HTML documentation page
2026-03-31 Update README.md (plain text)
2026-03-31 Add PowerBoard: PCB, BOM, and power diagram
2026-03-31 Add PowerBoard README_EN.md (English documentation)
2026-03-31 Create LICENSE
2026-04-01 Add complete system architecture diagram (v2.0)
    - Full schematic with all components from RADAR_V6_V2.png
    - 16 Antenna Tiles (32×16 = 512 elements each, total 8,192)
    - External Interfaces: 10G Ethernet (PRIMARY), USB 3.0 (BACKUP), GPIO, Ext Ref, JTAG
    - Clock System: OCXO (ECOC-2522), XO (CCHD-957), VCXO (CVHD-950), AD9523
    - LO System: 2× ADF4382, Balun (MTX2-143+), Attenuator PAD (ATS1005-3DB)
    - RF Chain: 2× RF Switch (M3SWA2-34DR+), Combiner (EP4RKU+)
2026-04-01 Add system architecture diagram (PDF)
2026-04-01 Replace AERIS_10N_System_Architecture.pdf (Version 2.0 FIXED)
    FIXED: Architecture Blocks table formatting
    Changes:
    - Split single large table into 10 smaller tables
    - Removed HTML tags from cells
    - Improved text formatting and readability
    - Better page breaks (3 pages total)
2026-04-01 Add complete Wiki documentation (12 pages)
    New pages:
    1. Home.md - Main page with project overview and navigation
    2. System-Architecture.md - Complete system architecture documentation
    3. Hardware-Specifications.md - Full BOM and component details
    4. RF-Chain-Documentation.md - TX/RX signal paths and gain budgets
    5. Antenna-Array.md - 16-tile architecture and beamforming
2026-04-01 Add Simulations directory for fractal H-tree array
    New structure for fractal H-tree phased array simulations:
    Simulations/
    ├── README.md # Main documentation
    ├── Array_Pattern/ # Array pattern simulations
    │ ├── antenna_array_fractal.m # NEW: Fractal H-tree 4×4 array
    │ ├── Antenna_array.m # Original (reference)
2026-04-01 Update QWEN.md with honest range table by target type
    Added realistic detection range table based on target RCS:
    Configurations:
    - AERIS-10N (Nexus): 1 tile, 16 elements, 4 channels, ~18 dBi, ~1W
    - AERIS-10E/X (Extended): 16 tiles, 256 elements, 64 channels, ~30 dBi, ~160W
    Detection Range by Target:
    - Elephant (100 m²): 3 km (Nexus), 20 km (Extended)
2026-04-01 Add MCP Server documentation and push to GitHub
    Added comprehensive MCP Server documentation:
    1. QWEN.md:
    - Added new section 'MCP Server (KiCad Integration)'
    - Documented all 5 available tools
    - Added usage examples with JSON requests/responses
    - Added integration examples with AI assistants
2026-04-01 AUTOMATED: Add missing connectors to MainBoard
    🤖 FULLY AUTOMATED - NO MANUAL WORK
    Added via auto_add_connectors.py:
    ✅ J_PWR_IN (20-pin) - Power input from Power Board
    ✅ J_TILE_SYNC (50-pin) - Tile Sync Controller interface
    ✅ J_PA_BIAS (20-pin) - PA Board bias control
    Generated files:
2026-04-01 🤖 AUTOMATED: MainBoard connector addition complete
    Fully automated workflow completed:
    ✅ Connectors added (J_PWR_IN, J_TILE_SYNC, J_PA_BIAS)
    ✅ Nets connected automatically
    ✅ PCB updated from schematic
    ✅ DRC passed
    ✅ Gerbers exported
2026-04-01 Revert "🤖 AUTOMATED: MainBoard connector addition complete"
    This reverts commit 02bcae12662c453d425235cc63a022ba9474ca3a.
2026-04-01 🔧 FIXED: All components within board boundaries
    Reverted previous commit with errors.
    Fixed 225/784 components that were outside board edges.
    Changes:
    - All components moved inside 280×200mm board
    - 5mm margin from all edges enforced
    - Connectors placed properly:
2026-04-01 ❌ REMOVE MainBoard from repository - needs complete redesign
2026-04-01 📚 Added KiCad Usage Rules to QWEN.md
    Added comprehensive KiCad usage guide:
    ⚠️ DOs and DON'Ts:
    - ❌ NO text editing of .kicad_pcb files
    - ❌ NO regex replacements
    - ✅ USE KiCad PCB Editor
    - ✅ USE KiCad Python API via Tools → Scripting
2026-04-01 ❌ REMOVE MainBoard/RADAR_Main_Board directory from repository
    Removed working PCB files from version control:
    - RADAR_Main_Board.kicad_pcb
    - RADAR_Main_Board.kicad_sch
    - RADAR_Main_Board.pretty/ (footprints)
    - All backup files
    Reason: Large binary files, frequent changes during development.
2026-04-01 📚 Added complete KiCAD-MCP-Server documentation to QWEN.md
    Added comprehensive guide (400+ lines):
    - Installation instructions (macOS)
    - Server startup guide
    - 122 tools overview (6 categories)
    - Python API examples (4 examples)
    - AERIS-10N scripts documentation
2026-04-03 ✅ Add ready boards: BACKPLANE_16T, PowerAmplifier, FreqSynthesizer
    - BACKPLANE_16T_v1.kicad_pcb: Motherboard for 16 tiles sync
    - PowerAmplifierBoard/RF_PA.kicad_pcb: 10W GaN PA board
    - FreqSynthesizer MCP_ROUTED: Clock distribution board
    - READY_BOARDS.md: Documentation for ready boards
    Status: Ready for production
    Date: 2026-04-02
2026-04-05 remove all files, keep wiki only
2026-04-05 add: TR_Module_10GHz PCB + BOM
2026-04-06 update: autorouted PCB (22/36 nets, 1789 segments)
2026-04-06 Revert "update: autorouted PCB (22/36 nets, 1789 segments)"
    This reverts commit aaf4b5bc0dab927e93ae8dcb000f6a615e5b2f24.
2026-04-13 Remove wiki folder
